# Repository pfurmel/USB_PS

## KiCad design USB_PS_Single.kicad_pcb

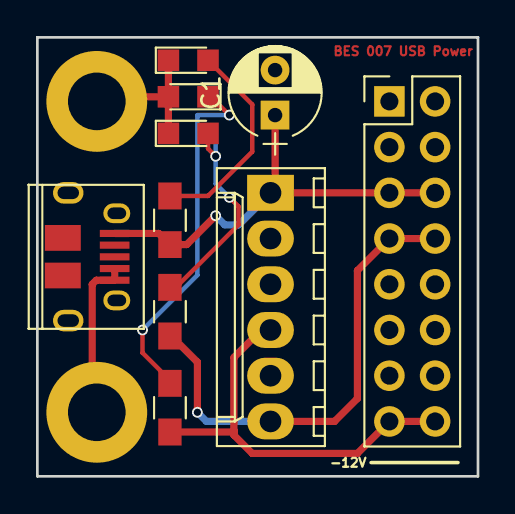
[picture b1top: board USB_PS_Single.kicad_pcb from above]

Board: 2 copper layers, 24.5 x 24.4 mm, 12 parts (0 on the bottom side), 7 nets.

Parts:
C1: CP1; CP_Radial_D5.0mm_P2.50mm
D1, D2, D3: LED; LED_0805
P1: CONN_02X08; Pin_Header_Straight_2x08_Pitch2.54mm
P2: CONN_01X06; Molex_KK-6410-06_06x2.54mm_Straight
P3: USB_B; USB_Micro-B_10103594-0001LF
P4, P5: CONN_01X01; MountingHole_3.2mm_M3_DIN965_Pad
R1, R2, R3: R; R_0805_HandSoldering

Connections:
+5V: C1.1, P1.5, P1.6, P2.1, P3.1, R3.2
+12V: P1.7, P1.8, P2.6, R1.2
GND: C1.2, D1.1, D2.2, D3.1, P1.9, P1.10, P1.11, P1.12, P1.13, P1.14, P2.2, P2.5, P3.4, P3.5, P4.1, P5.1
unnamed: D1.2, R1.1
unnamed: D2.1, R2.1
unnamed: D3.2, R3.1
VDD: P1.15, P1.16, P2.4, R2.2

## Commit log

2018-02-07 Updated labels
